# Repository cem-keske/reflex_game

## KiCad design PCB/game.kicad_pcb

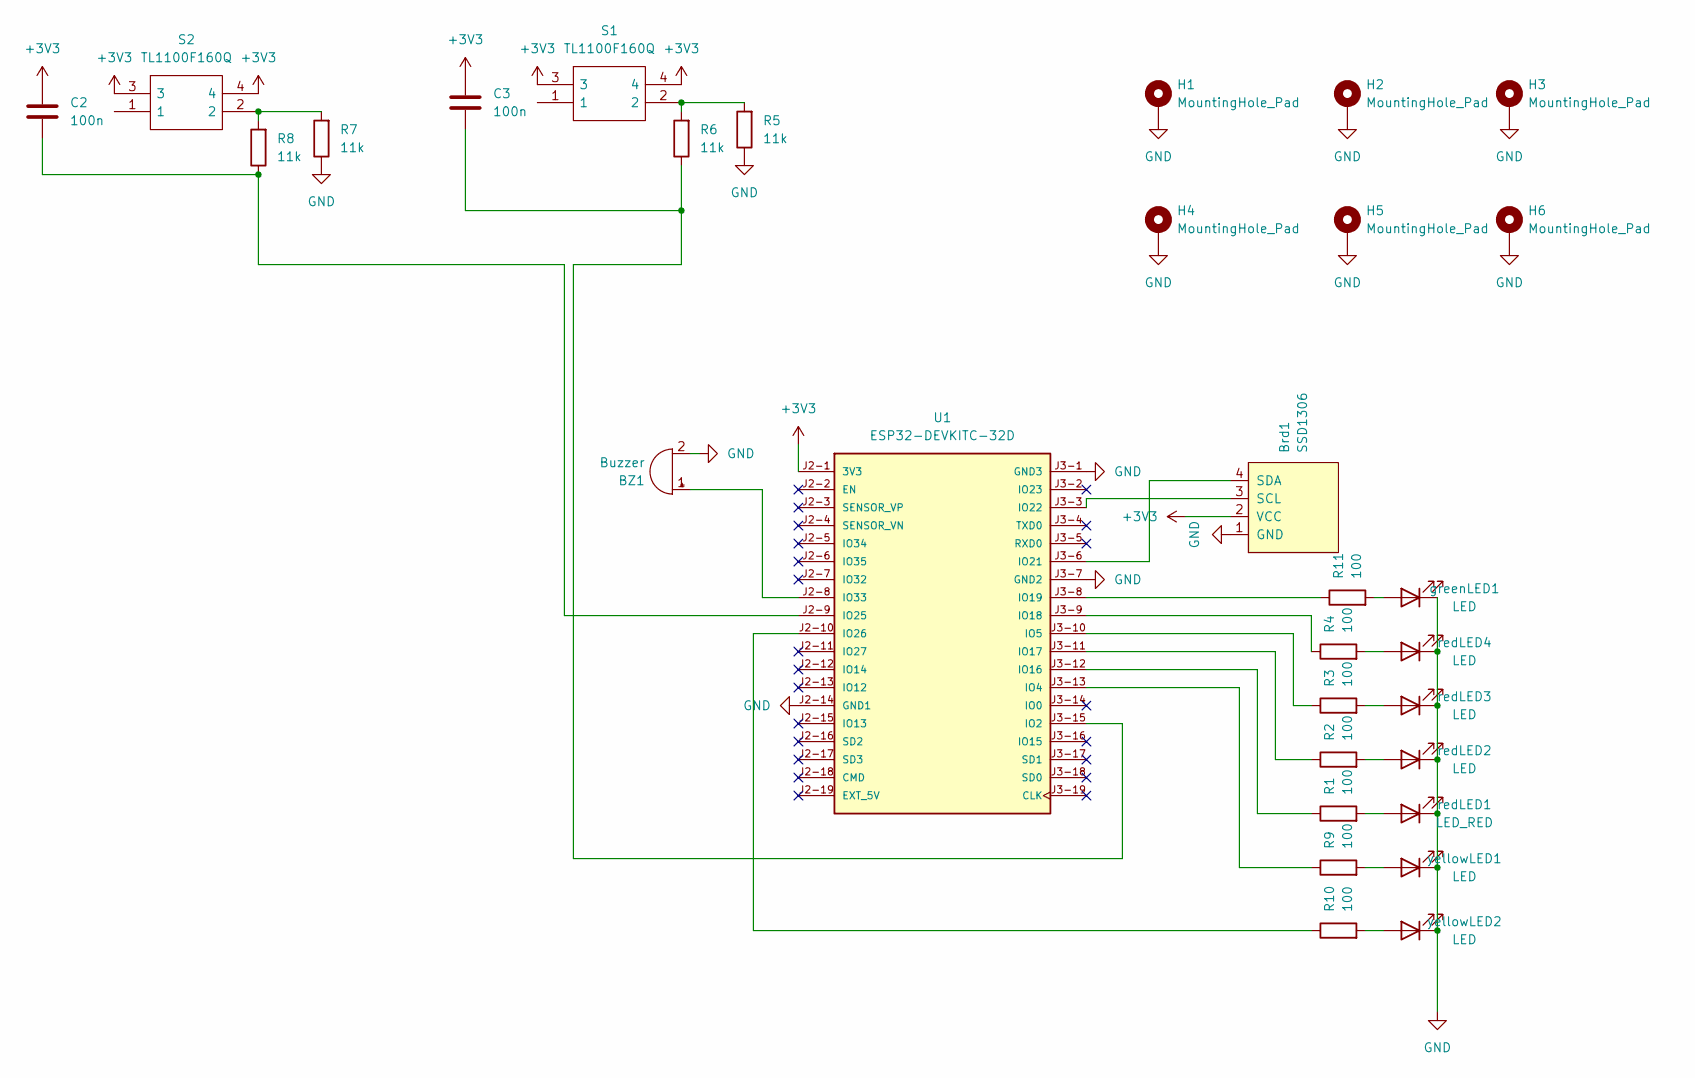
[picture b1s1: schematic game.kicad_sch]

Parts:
BZ1: Buzzer; Buzzer_12x9.5RM7.6
Brd1: SSD1306; OLED_display_SSD1306
C2, C3: 100n; CP_Radial_Tantal_D4.5mm_P5.00mm
H1, H2, H3, H4, H5, H6: MountingHole_Pad; MountingHole_3.2mm_M3_ISO7380_Pad_TopBottom
R1, R2, R3, R4, R9, R10, R11: 100; R_Axial_DIN0309_L9.0mm_D3.2mm_P12.70mm_Horizontal
R5, R6, R7, R8: 11k; R_Axial_DIN0309_L9.0mm_D3.2mm_P12.70mm_Horizontal
S1, S2: TL1100F160Q; Mouser Part Number 612-TL1100
U1: ESP32-DEVKITC-32D; MODULE_ESP32-DEVKITC-32D; PARTREV V4
greenLED1: LED; LED_D5.0mm
redLED1: LED_RED; LED_D5.0mm
redLED2, redLED3, redLED4: LED; LED_D5.0mm
yellowLED1, yellowLED2: LED; LED_D5.0mm

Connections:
+3V3: Brd1.2 (VCC), C2.1, C3.1, S1.3, S1.4, S2.3, S2.4, U1.J2-1 (3V3)
GND: BZ1.2 (+), Brd1.1 (GND), H1.1, H2.1, H3.1, H4.1, H5.1, H6.1, R5.1, R7.1, U1.J2-14 (GND1), U1.J3-1 (GND3), U1.J3-7 (GND2), greenLED1.1 (K), redLED1.1 (K), redLED2.1 (K), redLED3.1 (K), redLED4.1 (K), yellowLED1.1 (K), yellowLED2.1 (K)
unnamed: BZ1.1 (-), U1.J2-8 (IO33)
unnamed: Brd1.3 (SCL), U1.J3-3 (IO22)
unnamed: Brd1.4 (SDA), U1.J3-6 (IO21)
unnamed: R5.2, R6.2, S1.2
unnamed: R7.2, R8.2, S2.2
unnamed: C3.2, R6.1, U1.J3-15 (IO2)
unnamed: R9.1, U1.J3-13 (IO4)
unnamed: R3.1, U1.J3-10 (IO5)
unnamed: R1.1, U1.J3-12 (IO16)
unnamed: R2.1, U1.J3-11 (IO17)
unnamed: R4.1, U1.J3-9 (IO18)
unnamed: R11.1, U1.J3-8 (IO19)
unnamed: C2.2, R8.1, U1.J2-9 (IO25)
unnamed: R10.1, U1.J2-10 (IO26)
unnamed: R11.2, greenLED1.2 (A)
unnamed: R1.2, redLED1.2 (A)
unnamed: R2.2, redLED2.2 (A)
unnamed: R3.2, redLED3.2 (A)
unnamed: R4.2, redLED4.2 (A)
unnamed: R9.2, yellowLED1.2 (A)
unnamed: R10.2, yellowLED2.2 (A)

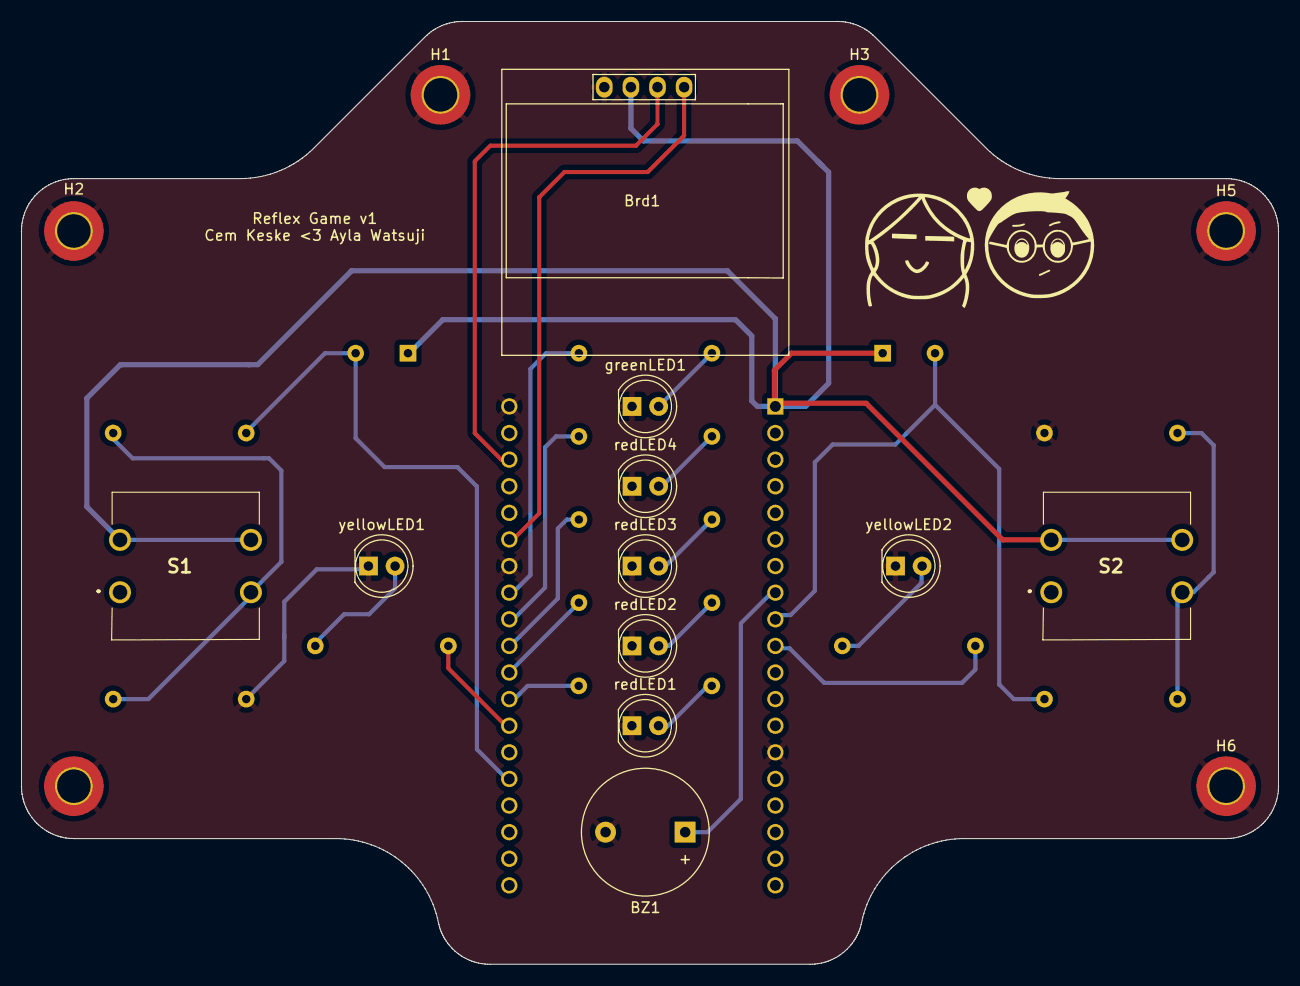
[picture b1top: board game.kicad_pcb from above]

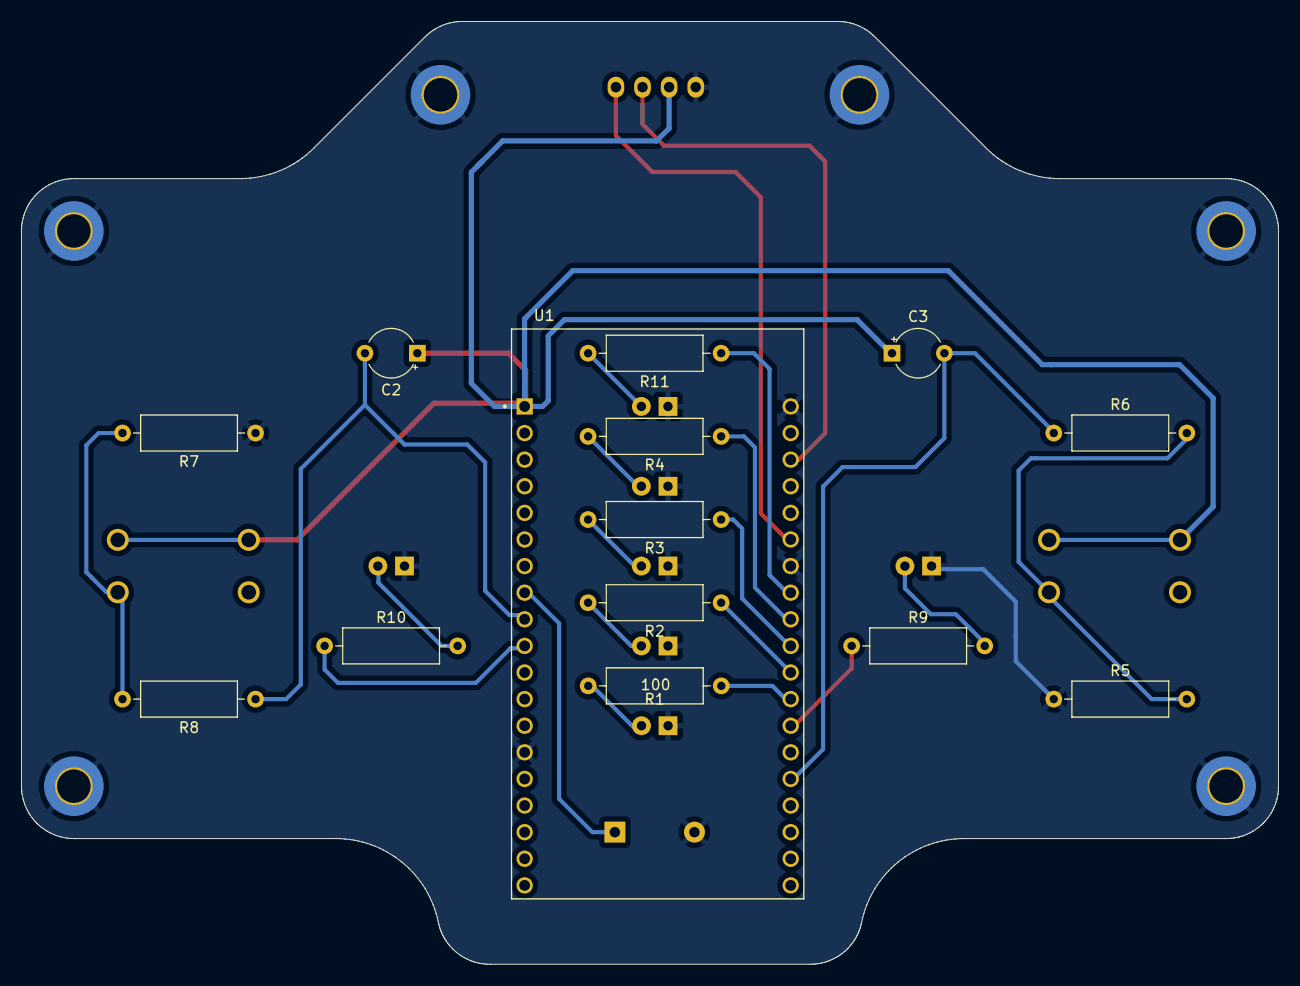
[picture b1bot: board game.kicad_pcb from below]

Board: 2 copper layers, 120.0 x 90.0 mm, 31 parts (14 on the bottom side), 23 nets.

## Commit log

2024-08-11 clean up folder
2024-08-11 adding new folders
2024-08-11 arduino compliance
2024-08-11 Git ignore added
2024-08-11 Include statements fixed
2024-08-11 display added
2024-08-12 Buzzer implemented and tested
2024-08-13 Code modularity and Game class implemented
2024-08-13 aduino compability
2024-08-13 bug fixes
2024-09-02 PCB added
